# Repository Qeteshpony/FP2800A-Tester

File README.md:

# FP2800A-Tester

[Hardware Documentation](https://qeteshpony.github.io/FP2800A-Tester)

Arduino Uno compatible shield for testing functionality of a FP2800A

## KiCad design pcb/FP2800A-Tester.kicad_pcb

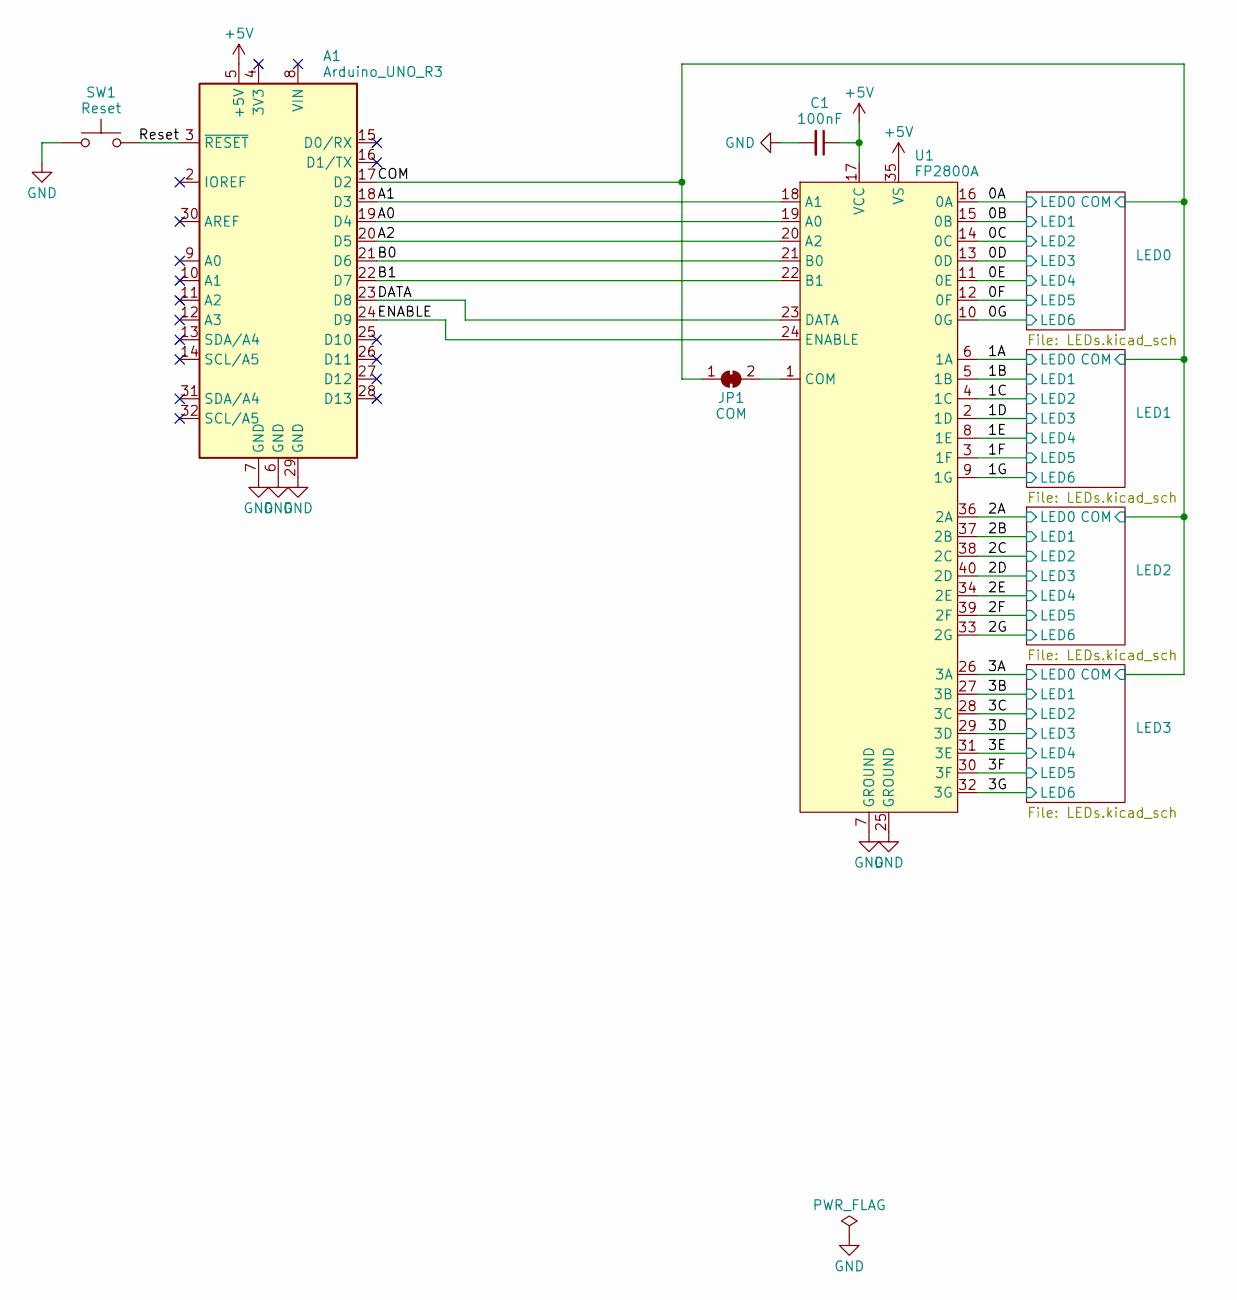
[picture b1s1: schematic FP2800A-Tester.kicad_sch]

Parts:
A1: Arduino_UNO_R3
C1: 100nF; C_0603_1608Metric; LCSC C14663
JP1: COM; SolderJumper-2_P1.3mm_Bridged_RoundedPad1.0x1.5mm
SW1: Reset; SW_PUSH_6mm
U1: FP2800A; DIP_Socket-40_W11.9_W12.7_W15.24_W17.78_W18.5_3M_240-1280-0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

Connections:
+5V: A1.5 (+5V), C1.1, U1.17 (VCC), U1.35 (VS)
/0A: U1.16 (0A); also elsewhere on the board
/0B: U1.15 (0B); also elsewhere on the board
/0C: U1.14 (0C); also elsewhere on the board
/0D: U1.13 (0D); also elsewhere on the board
/0E: U1.11 (0E); also elsewhere on the board
/0F: U1.12 (0F); also elsewhere on the board
/0G: U1.10 (0G); also elsewhere on the board
/1A: U1.6 (1A); also elsewhere on the board
/1B: U1.5 (1B); also elsewhere on the board
/1C: U1.4 (1C); also elsewhere on the board
/1D: U1.2 (1D); also elsewhere on the board
/1E: U1.8 (1E); also elsewhere on the board
/1F: U1.3 (1F); also elsewhere on the board
/1G: U1.9 (1G); also elsewhere on the board
/2A: U1.36 (2A); also elsewhere on the board
/2B: U1.37 (2B); also elsewhere on the board
/2C: U1.38 (2C); also elsewhere on the board
/2D: U1.40 (2D); also elsewhere on the board
/2E: U1.34 (2E); also elsewhere on the board
/2F: U1.39 (2F); also elsewhere on the board
/2G: U1.33 (2G); also elsewhere on the board
/3A: U1.26 (3A); also elsewhere on the board
/3B: U1.27 (3B); also elsewhere on the board
/3C: U1.28 (3C); also elsewhere on the board
/3D: U1.29 (3D); also elsewhere on the board
/3E: U1.31 (3E); also elsewhere on the board
/3F: U1.30 (3F); also elsewhere on the board
/3G: U1.32 (3G); also elsewhere on the board
/A0: A1.19 (D4), U1.19 (A0)
/A1: A1.18 (D3), U1.18 (A1)
/A2: A1.20 (D5), U1.20 (A2)
/B0: A1.21 (D6), U1.21 (B0)
/B1: A1.22 (D7), U1.22 (B1)
/COM: A1.17 (D2), JP1.1 (A); also elsewhere on the board
/DATA: A1.23 (D8), U1.23 (DATA)
/ENABLE: A1.24 (D9), U1.24 (ENABLE)
/Reset: A1.3 (~RESET), SW1.2
GND: A1.6 (GND), A1.7 (GND), A1.29 (GND), C1.2, SW1.1, U1.7 (GROUND), U1.25 (GROUND)
unnamed: JP1.2 (B), U1.1 (COM)

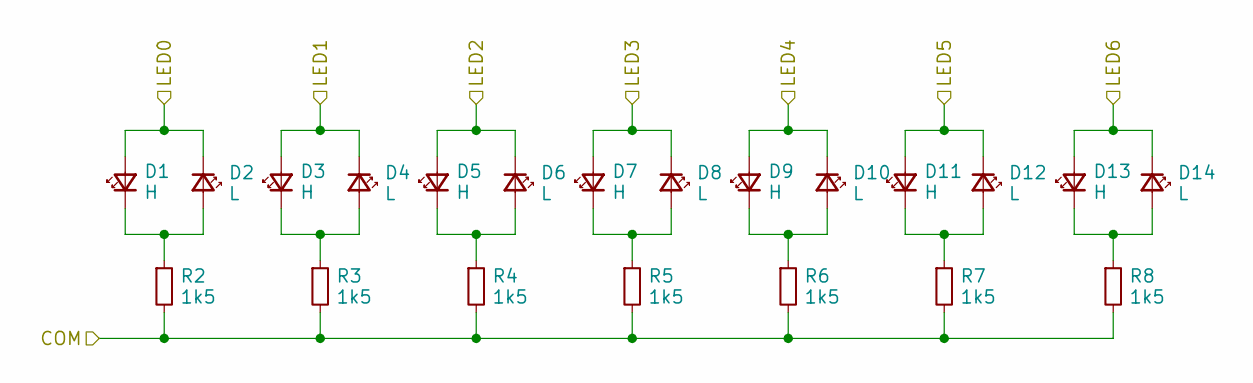
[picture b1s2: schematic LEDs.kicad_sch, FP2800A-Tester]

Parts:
D1, D3, D5, D7, D9, D11, D13: H; LED_0603_1608Metric; LCSC C72043
D2, D4, D6, D8, D10, D12, D14: L; LED_0603_1608Metric; LCSC C2286
R2, R3, R4, R5, R6, R7, R8: 1k5; R_0603_1608Metric; LCSC C22843

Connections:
/0A: D1.2 (A), D2.1 (K); also elsewhere on the board
/0B: D3.2 (A), D4.1 (K); also elsewhere on the board
/0C: D5.2 (A), D6.1 (K); also elsewhere on the board
/0D: D7.2 (A), D8.1 (K); also elsewhere on the board
/0E: D9.2 (A), D10.1 (K); also elsewhere on the board
/0F: D11.2 (A), D12.1 (K); also elsewhere on the board
/0G: D13.2 (A), D14.1 (K); also elsewhere on the board
/COM: R2.2, R3.2, R4.2, R5.2, R6.2, R7.2, R8.2; also elsewhere on the board
unnamed: D1.1 (K), D2.2 (A), R2.1
unnamed: D3.1 (K), D4.2 (A), R3.1
unnamed: D5.1 (K), D6.2 (A), R4.1
unnamed: D7.1 (K), D8.2 (A), R5.1
unnamed: D9.1 (K), D10.2 (A), R6.1
unnamed: D11.1 (K), D12.2 (A), R7.1
unnamed: D13.1 (K), D14.2 (A), R8.1

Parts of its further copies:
D15, D17, D19, D21, D23, D25, D27, D29, D31, D33, D35, D37, D39, D41, D43, D45, D47, D49, D51, D53, D55: H; LED_0603_1608Metric; LCSC C72043
D16, D18, D20, D22, D24, D26, D28, D30, D32, D34, D36, D38, D40, D42, D44, D46, D48, D50, D52, D54, D56: L; LED_0603_1608Metric; LCSC C2286
R9, R10, R11, R12, R13, R14, R15, R16, R17, R18, R19, R20, R21, R22, R23, R24, R25, R26, R27, R28, R29: 1k5; R_0603_1608Metric; LCSC C22843

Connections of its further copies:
/1A: D15.2 (A), D16.1 (K); also elsewhere on the board
/1B: D17.2 (A), D18.1 (K); also elsewhere on the board
/1C: D19.2 (A), D20.1 (K); also elsewhere on the board
/1D: D21.2 (A), D22.1 (K); also elsewhere on the board
/1E: D23.2 (A), D24.1 (K); also elsewhere on the board
/1F: D25.2 (A), D26.1 (K); also elsewhere on the board
/1G: D27.2 (A), D28.1 (K); also elsewhere on the board
/2A: D29.2 (A), D30.1 (K); also elsewhere on the board
/2B: D31.2 (A), D32.1 (K); also elsewhere on the board
/2C: D33.2 (A), D34.1 (K); also elsewhere on the board
/2D: D35.2 (A), D36.1 (K); also elsewhere on the board
/2E: D37.2 (A), D38.1 (K); also elsewhere on the board
/2F: D39.2 (A), D40.1 (K); also elsewhere on the board
/2G: D41.2 (A), D42.1 (K); also elsewhere on the board
/3A: D43.2 (A), D44.1 (K); also elsewhere on the board
/3B: D45.2 (A), D46.1 (K); also elsewhere on the board
/3C: D47.2 (A), D48.1 (K); also elsewhere on the board
/3D: D49.2 (A), D50.1 (K); also elsewhere on the board
/3E: D51.2 (A), D52.1 (K); also elsewhere on the board
/3F: D53.2 (A), D54.1 (K); also elsewhere on the board
/3G: D55.2 (A), D56.1 (K); also elsewhere on the board
/COM: R9.2, R10.2, R11.2, R12.2, R13.2, R14.2, R15.2, R16.2, R17.2, R18.2, R19.2, R20.2, R21.2, R22.2, R23.2, R24.2, R25.2, R26.2, R27.2, R28.2, R29.2; also elsewhere on the board
unnamed: D15.1 (K), D16.2 (A), R9.1
unnamed: D17.1 (K), D18.2 (A), R10.1
unnamed: D19.1 (K), D20.2 (A), R11.1
unnamed: D21.1 (K), D22.2 (A), R12.1
unnamed: D23.1 (K), D24.2 (A), R13.1
unnamed: D25.1 (K), D26.2 (A), R14.1
unnamed: D27.1 (K), D28.2 (A), R15.1
unnamed: D29.1 (K), D30.2 (A), R16.1
unnamed: D31.1 (K), D32.2 (A), R17.1
unnamed: D33.1 (K), D34.2 (A), R18.1
unnamed: D35.1 (K), D36.2 (A), R19.1
unnamed: D37.1 (K), D38.2 (A), R20.1
unnamed: D39.1 (K), D40.2 (A), R21.1
unnamed: D41.1 (K), D42.2 (A), R22.1
unnamed: D43.1 (K), D44.2 (A), R23.1
unnamed: D45.1 (K), D46.2 (A), R24.1
unnamed: D47.1 (K), D48.2 (A), R25.1
unnamed: D49.1 (K), D50.2 (A), R26.1
unnamed: D51.1 (K), D52.2 (A), R27.1
unnamed: D53.1 (K), D54.2 (A), R28.1
unnamed: D55.1 (K), D56.2 (A), R29.1

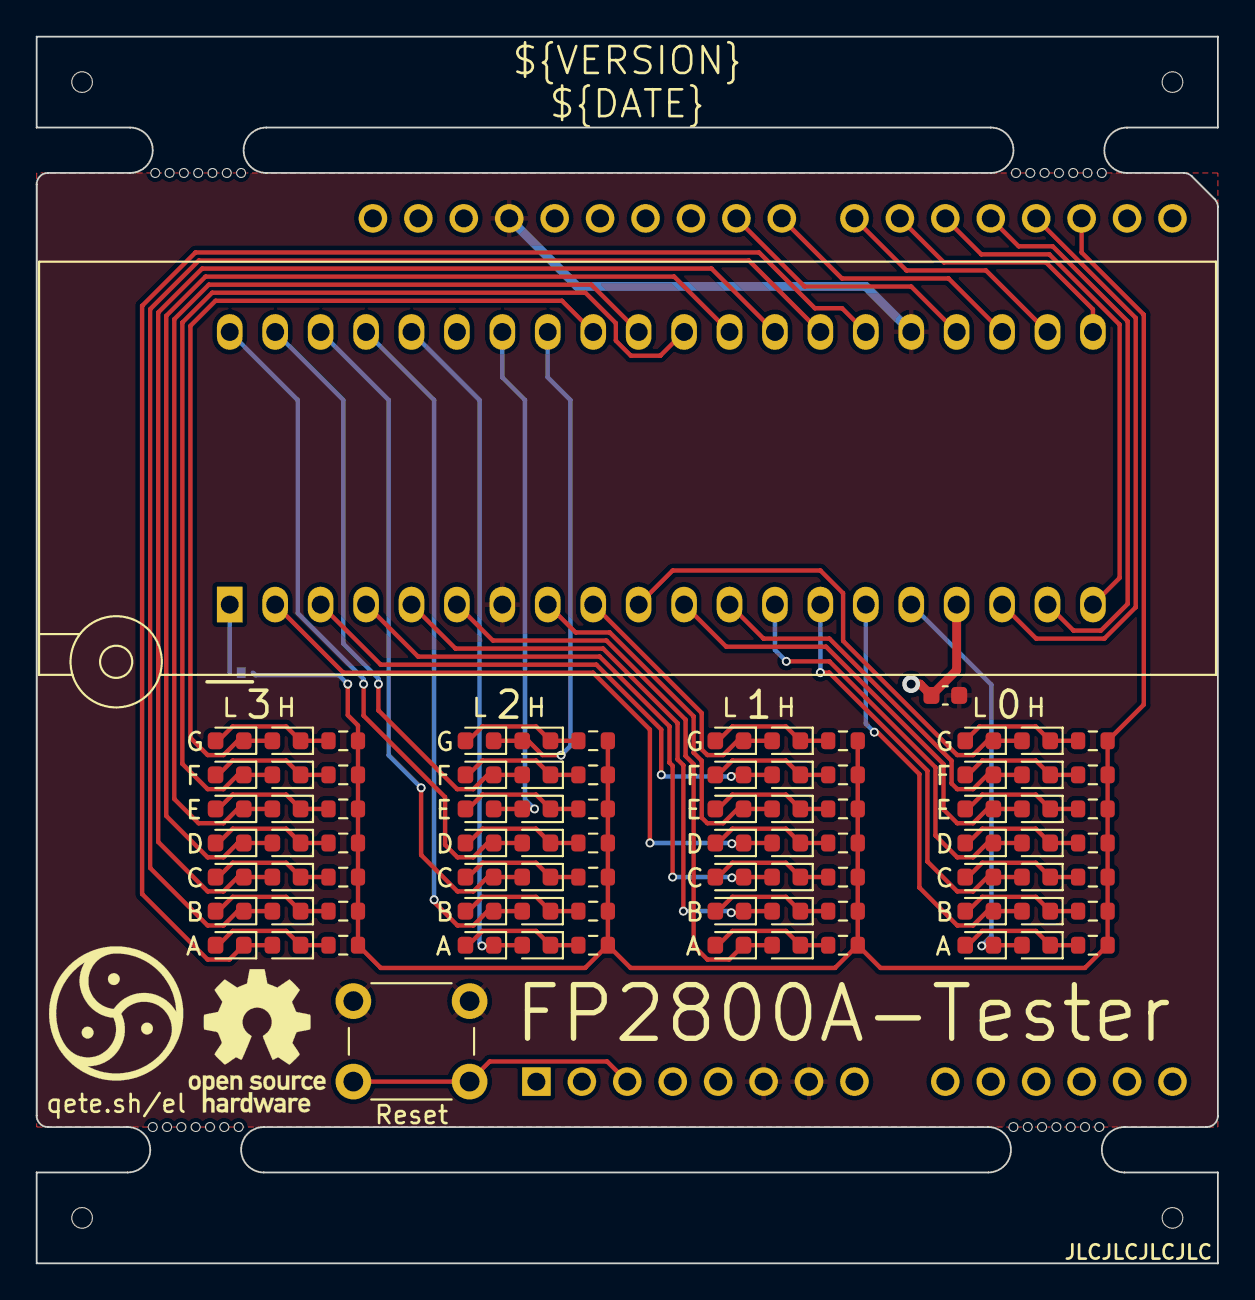
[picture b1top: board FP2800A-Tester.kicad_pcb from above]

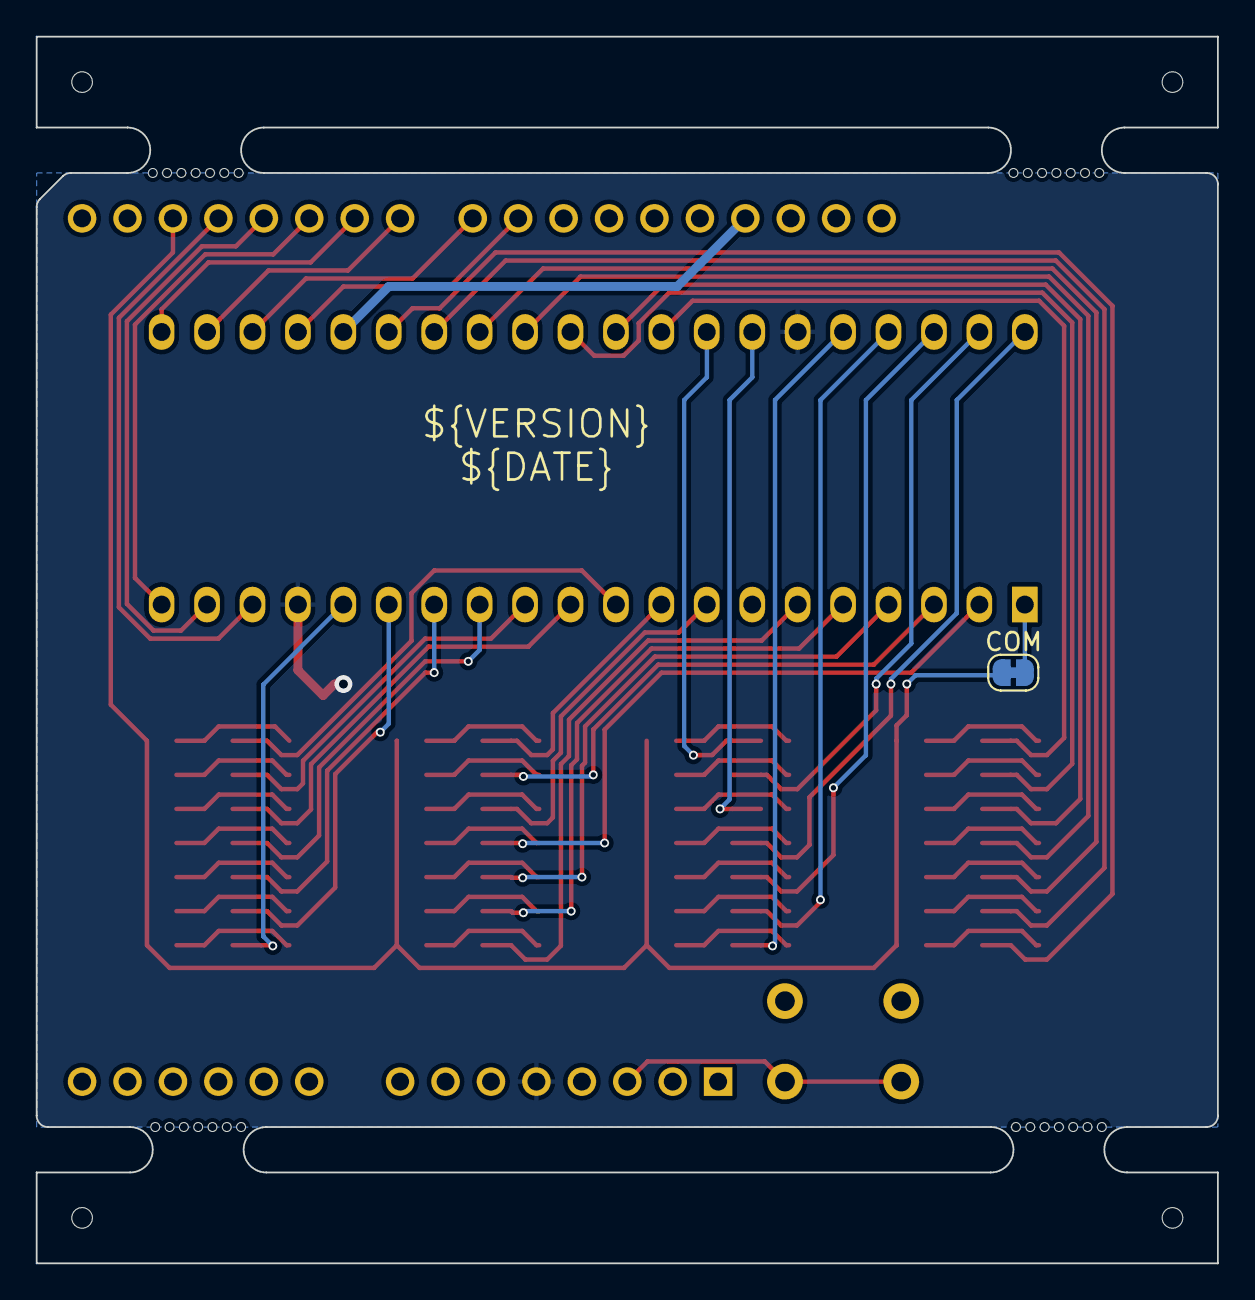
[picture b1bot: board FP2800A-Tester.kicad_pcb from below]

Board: 2 copper layers, 66.0 x 68.6 mm, 89 parts (2 on the bottom side), 68 nets.

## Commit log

2023-07-03 feat: initial commit
2023-07-03 style: add variables
2023-07-03 feat: add rails
2023-07-03 feat: add part numbers for production
2023-07-03 chore(main): release 1.0.0
2023-07-03 style: schematics cleanup
2023-07-04 feat: add COM Jumper
    Add a jumper that allows to disconnect the FP2800A COM pin from the LEDs
2023-07-04 chore(main): release 1.1.0
2023-07-04 feat: initial code release
2023-07-10 fix: turn the loops around
    Making the loops count down instead of up to make the LED light up in a nicer order. Also added some comments
2023-07-10 feat: replace IC socket with ZIF socket
2023-07-10 chore(main): release 1.2.0
2024-08-29 ci: remove dependency between jobs
